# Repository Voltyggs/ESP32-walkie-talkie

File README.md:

<h1>ESP TALK - the off grid solution to communication</h1>

ESP TALK is a walkie talkie based on the ESP32 and the ESPNOW protocol to provide a off gid communication medium

<br>

<h3>This is the schematic of my walkie talkie. The project consists of an esp32, mic, speaker, audio amplifier + DAC, and dual power supplies <br>
The i2s Mic first transmits its audio signals to the esp32 when the PTT button is held. After, the esp32 transmits the audio packets to the 0xFF, 0xFF, 0xFF, 0xFF, 0xFF, 0xFF address. The nearby walkie talkies pick up the signal and play it through the speaker which is powered by an MAX98351 which also doubles as a DAC for the esp32 for a better audio</h3>

- Main Features:
  - Completely self dependent and off grid as it runs with ESPNOW
  - antenna for a better range
  - uses the 12 bit DAC of the MAX98351 rather than the esp32's 8 bit DAC
Here is the case:

How to assemble: <br>
Pretty straight forward, place the assembled pcb in the base housing, glue the lid. There are 2 slots for 5.95 x 2.54 neodymium magnets that needs ot be glued onto the external lip. It can be used as a cvover for when the mic is not in use. <br>
<br>
How to use:<br>
**MAKE SURE TO PAY ATTENTION TO THE MIC ORIENTATION DURING ASSEMBLY AS IT MIGHT NEED TO BE FLIPPED AND MAKE SURE TO FLASH THE ESP32 BEFORE ASSEMBLY**<br>
This is a fairly simple project, after assembling it, charge the batteries through the TP4096 module (make sure to turn off the load switches), edit the transmit aaddress or keep it as default (0xFF, 0xFF, 0xFF, 0xFF, 0xFF, 0xFF). After that, just hold down teh push to talk button and transmit!

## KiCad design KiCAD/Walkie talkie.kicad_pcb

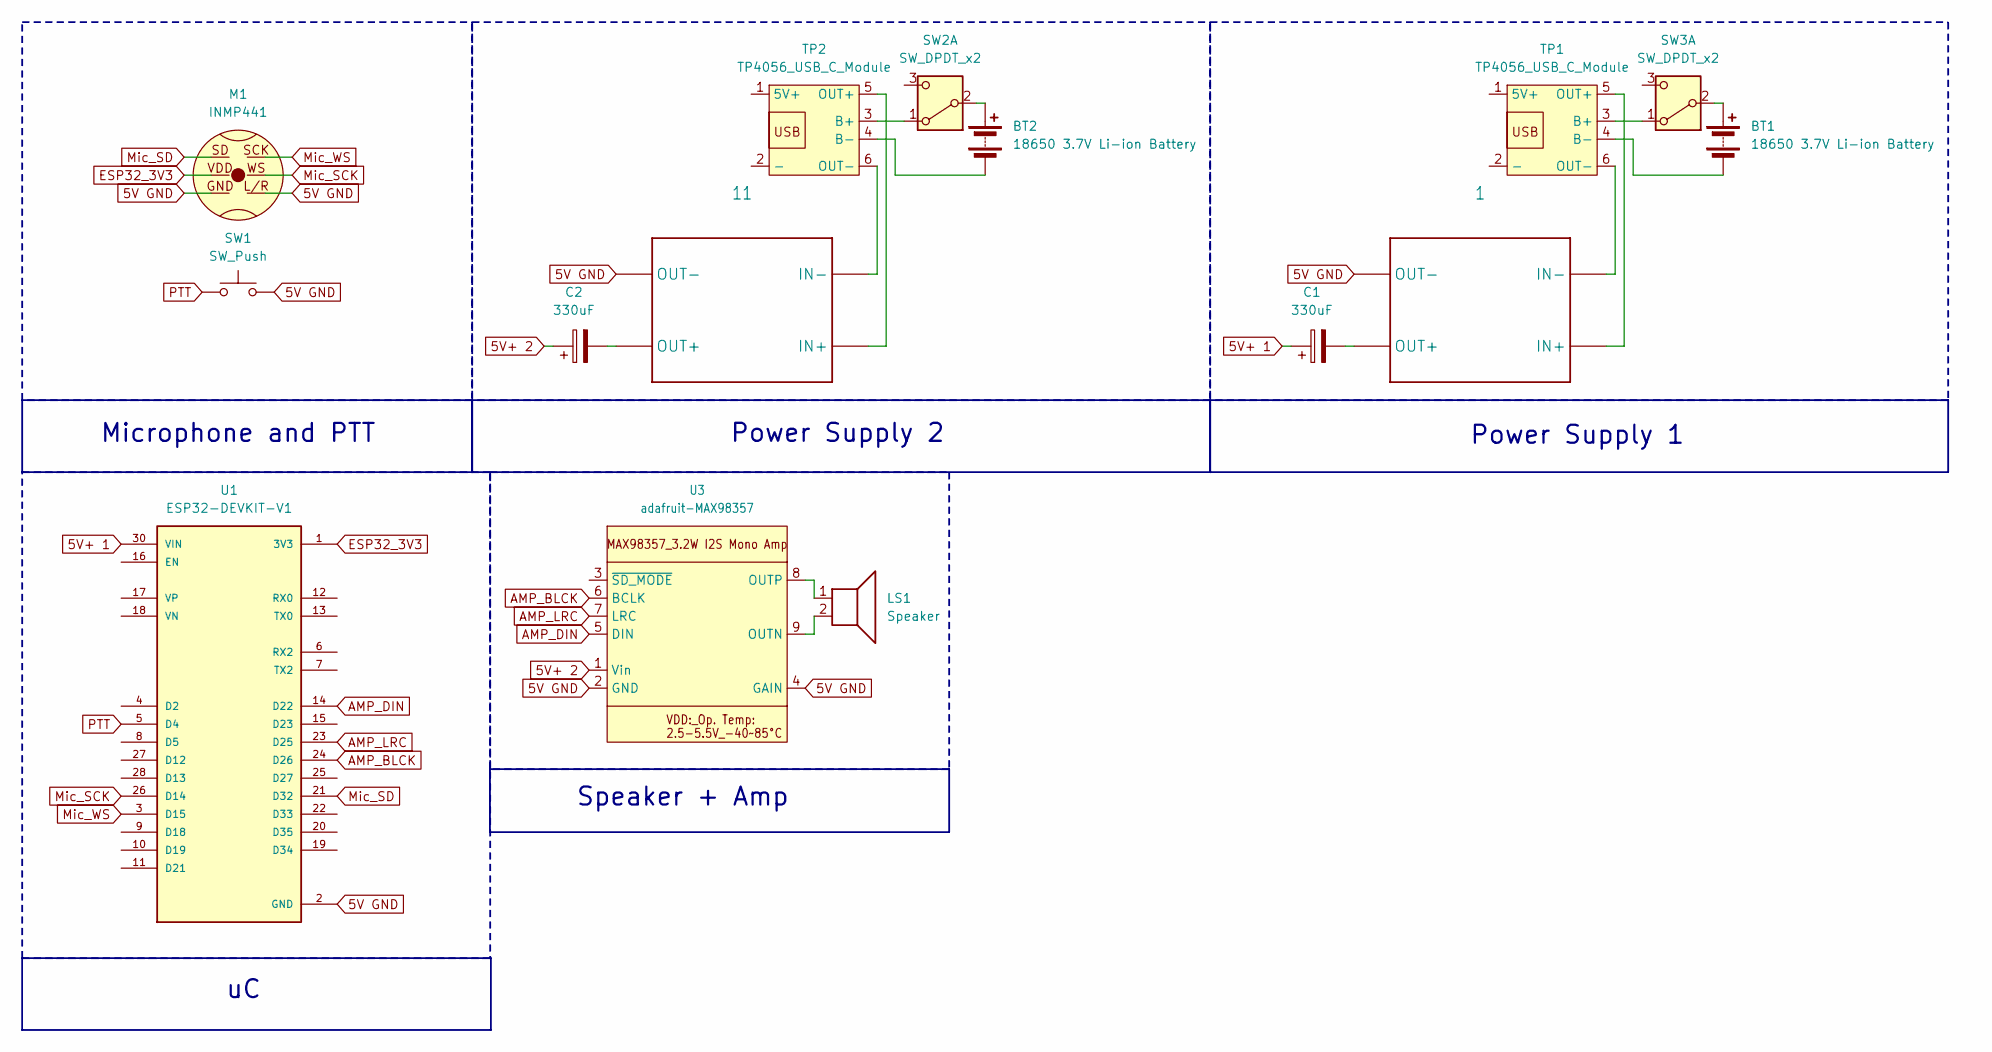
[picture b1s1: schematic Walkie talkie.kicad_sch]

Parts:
1, 11: hw-045
BT1, BT2: 18650 3.7V Li-ion Battery; BatteryHolder_MPD_BH-18650-PC
C1, C2: 330uF; C_Rect_L7.0mm_W4.5mm_P5.00mm
LS1: Speaker; 2_3W_8O_Speaker
M1: INMP441
SW1: SW_Push; SW_PUSH_6mm
SW2, SW3: SW_DPDT_x2; SW_CK_JS202011CQN_DPDT_Straight
TP1, TP2: TP4056_USB_C_Module; TP4056-18650
U1: ESP32-DEVKIT-V1; MODULE_ESP32_DEVKIT_V1; PARTREV N/A
U3: adafruit-MAX98357

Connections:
5V GND: 1.4 (OUT-), 11.4 (OUT-), M1.GND, M1.L/R, SW1.2, U1.2 (GND), U1.29 (GND), U3.2 (GND), U3.4 (GAIN)
5V+ 1: C1.1, U1.30 (VIN)
5V+ 2: C2.1, U3.1 (Vin)
AMP_BLCK: U1.24 (D26), U3.6 (BCLK)
AMP_DIN: U1.14 (D22), U3.5 (DIN)
AMP_LRC: U1.23 (D25), U3.7 (LRC)
ESP32_3V3: M1.VDD, U1.1 (3V3)
Mic_SCK: M1.WS, U1.26 (D14)
Mic_SD: M1.SD, U1.21 (D32)
Mic_WS: M1.SCK, U1.3 (D15)
unnamed: 1.2 (IN+), TP1.5 (OUT+)
unnamed: 1.1 (IN-), TP1.6 (OUT-)
unnamed: 1.3 (OUT+), C1.2
unnamed: 11.2 (IN+), TP2.5 (OUT+)
unnamed: 11.1 (IN-), TP2.6 (OUT-)
unnamed: 11.3 (OUT+), C2.2
unnamed: BT1.1 (+), SW3.2 (B)
unnamed: BT1.2 (-), TP1.4 (B-)
unnamed: BT2.1 (+), SW2.2 (B)
unnamed: BT2.2 (-), TP2.4 (B-)
unnamed: SW2.1 (A), TP2.3 (B+)
unnamed: SW3.1 (A), TP1.3 (B+)
unnamed: LS1.2, U3.9 (OUTN)
unnamed: LS1.1, U3.8 (OUTP)
PTT: SW1.1, U1.5 (D4)

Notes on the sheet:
Power Supply 2
Power Supply 1
Speaker + Amp
Microphone and PTT

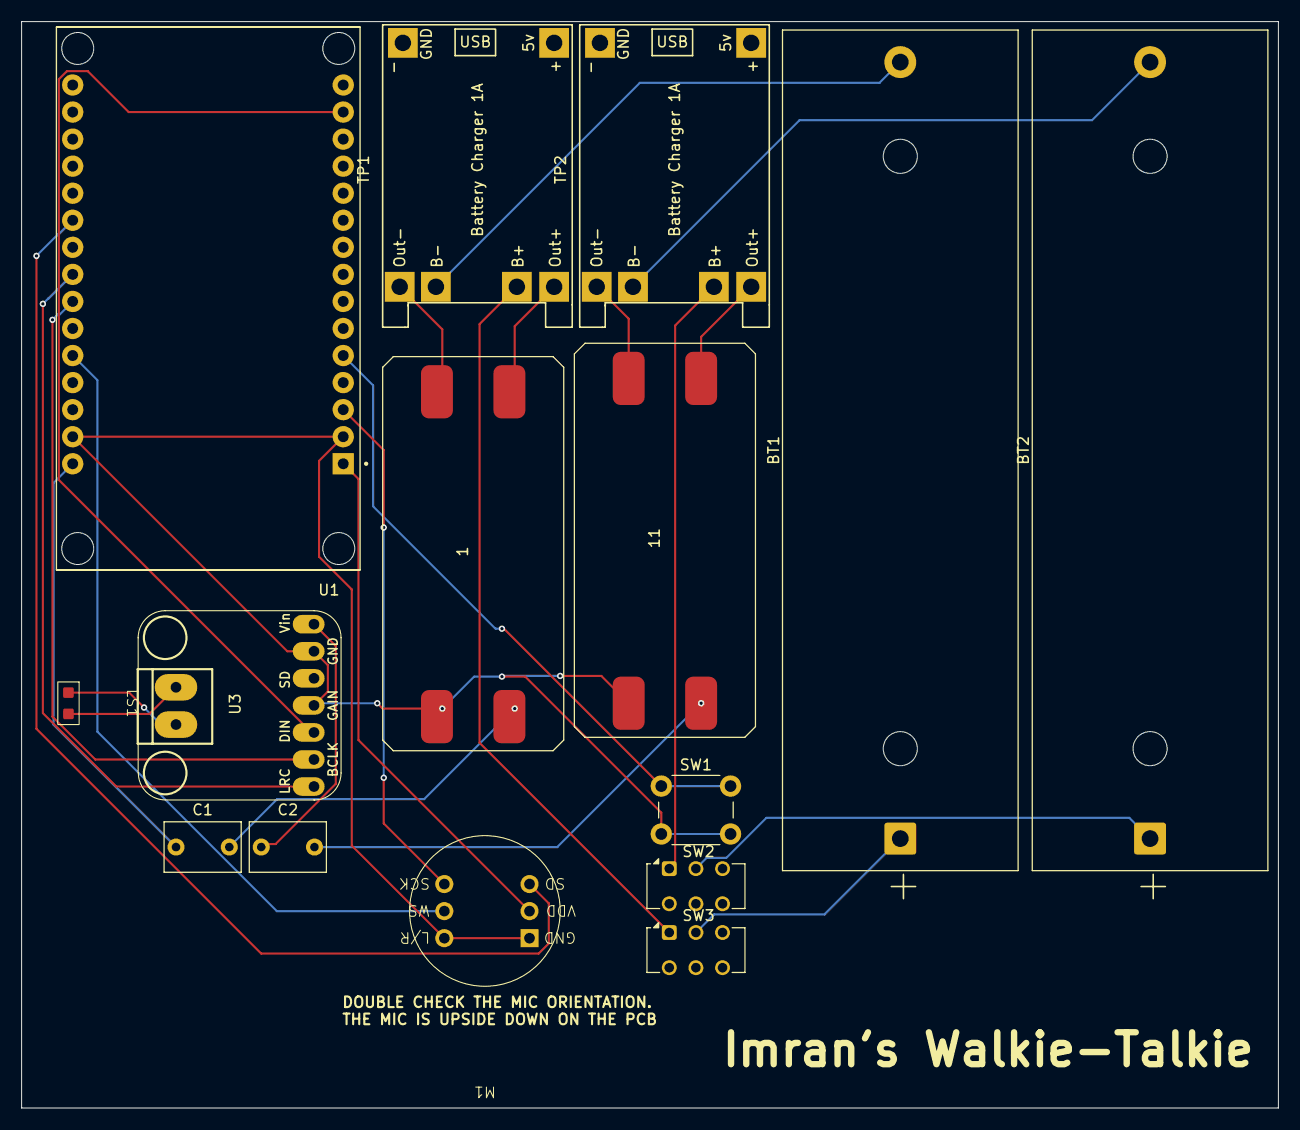
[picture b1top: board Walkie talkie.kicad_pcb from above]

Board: 2 copper layers, 118.0 x 102.0 mm, 15 parts (0 on the bottom side), 25 nets.

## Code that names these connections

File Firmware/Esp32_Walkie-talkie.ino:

#include <WiFi.h>
#include <esp_now.h>
#include <esp_wifi.h>
#include <driver/i2s.h>

#define PTT_PIN 4
#define MIC_SCK_PIN 14  
#define MIC_WS_PIN 33
#define MIC_SD_PIN 32
#define AMP_BCLK_PIN 26  
#define AMP_LRC_PIN 27  
#define AMP_DIN_PIN 25

#define SAMPLE_RATE 16000
#define BUFFER_SIZE 200 

uint8_t txBuffer[BUFFER_SIZE];
uint8_t broadcastAddress[] = {0xFF, 0xFF, 0xFF, 0xFF, 0xFF, 0xFF};

bool isTransmitting = false;




void OnDataRecv(const uint8_t * mac, const uint8_t *incomingData, int len) {
  if (digitalRead(PTT_PIN) == HIGH) {
    size_t bytesWritten = 0;
    i2s_write(I2S_NUM_1, incomingData, len, &bytesWritten, portMAX_DELAY);
  }
}

void initI2S() {
  i2s_config_t micConfig = {
    .mode = (i2s_mode_t)(I2S_MODE_MASTER | I2S_MODE_RX),
    .sample_rate = SAMPLE_RATE,
    .bits_per_sample = I2S_BITS_PER_SAMPLE_16BIT,
    .channel_format = I2S_CHANNEL_FMT_ONLY_LEFT,
    .communication_format = I2S_COMM_FORMAT_STAND_I2S,
    .intr_alloc_flags = ESP_INTR_FLAG_LEVEL1,
    .dma_buf_count = 4,
    .dma_buf_len = 100,
    .use_apll = false
  };

  i2s_pin_config_t micPins = {
    .bck_io_num = MIC_SCK_PIN,
    .ws_io_num = MIC_WS_PIN,
    .data_out_num = I2S_PIN_NO_CHANGE,
    .data_in_num = MIC_SD_PIN
  };

  i2s_driver_install(I2S_NUM_0, &micConfig, 0, NULL);
  i2s_set_pin(I2S_NUM_0, &micPins);

  i2s_config_t ampConfig = {
    .mode = (i2s_mode_t)(I2S_MODE_MASTER | I2S_MODE_TX),
    .sample_rate = SAMPLE_RATE,
    .bits_per_sample = I2S_BITS_PER_SAMPLE_16BIT,
    .channel_format = I2S_CHANNEL_FMT_ONLY_LEFT,
    .communication_format = I2S_COMM_FORMAT_STAND_I2S,
    .intr_alloc_flags = ESP_INTR_FLAG_LEVEL1,
    .dma_buf_count = 4,
    .dma_buf_len = 100,
    .use_apll = false
  };

  i2s_pin_config_t ampPins = {
    .bck_io_num = AMP_BCLK_PIN,
    .ws_io_num = AMP_LRC_PIN,
    .data_out_num = AMP_DIN_PIN,
    .data_in_num = I2S_PIN_NO_CHANGE
  };

  i2s_driver_install(I2S_NUM_1, &ampConfig, 0, NULL);
  i2s_set_pin(I2S_NUM_1, &ampPins);
}

void setup() {
  Serial.begin(115200);
  Serial.println("Booting");
  pinMode(PTT_PIN, INPUT_PULLUP);
  
  initI2S();
  Serial.println("Audio ok");

  WiFi.mode(WIFI_STA);
  esp_wifi_set_protocol(WIFI_IF_STA, WIFI_PROTOCOL_LR);

  if (esp_now_init() != ESP_OK) {
    Serial.println("espnoW error.");
    return;
  }
  
  esp_now_register_recv_cb(esp_now_recv_cb_t(OnDataRecv));
  esp_now_peer_info_t peerInfo = {};
  memcpy(peerInfo.peer_addr, broadcastAddress, 6);
  peerInfo.channel = 0;  
  peerInfo.encrypt = false;
  
  if (esp_now_add_peer(&peerInfo) != ESP_OK) {
    Serial.println("Failed to register broadcast channel");
    return;
  }
}

void loop() {
  bool buttonPressed = (digitalRead(PTT_PIN) == LOW);
  if (buttonPressed && !isTransmitting) {
    Serial.println("Mic open");
    isTransmitting = true;
  } 
  else if (!buttonPressed && isTransmitting) {
    Serial.println("mic closed");
    isTransmitting = false;
  }

  if (buttonPressed) {
    size_t bytesRead = 0;

    i2s_read(I2S_NUM_0, txBuffer, BUFFER_SIZE, &bytesRead, portMAX_DELAY);
    
    if (bytesRead > 0) {
      esp_now_send(broadcastAddress, txBuffer, bytesRead);
    }
  }
}
